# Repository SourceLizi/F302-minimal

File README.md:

# STM32F302C8T6最小系统

这个硬件项目是用于取代原先F103C8T6开发板而制作的，也为其他硬件项目提供参考。相比于同等密度的F103，STM32F302拥有一个高速（5MSPS）ADC，并且额外增加了一个运放和三个比较器，适合模数混合的应用。另外由于其定时器带有输入时钟倍频的功能，其输出分辨率比F103更高。

板载功能除了必须的调试口，复位电路以及晶振电路之外，还引出了USB接口与两枚测试用的LED，另外还增加了一颗IMU（QMI8658C）的位置，用于实践测试IMU解算算法以及评估IMU性能。

最小系统板还配备了一块带有三个半桥驱动的底板（原来的目的是用于驱动电机，后面发现不符合要求），适合用于作为功率级使用。三个半桥均带有电流检测的功能。由核心板的5V经过升压达到11V输入驱动IC，而电流检测放大器的供电则由5V经线性稳压供电。

## 硬件说明

1. 最小系统板内主控的模拟电源与数字电源可分开供电，可以选择使用额外的LDO LP5907为模拟电源供电，或者拖锡连接JP1直接连接模数电源

2. AMS1117输入输出的二极管D3必须焊接，否则会出现在调试时只接入3.3V而1117发热严重的情况

3. IMU的中断管脚INT1与栅极驱动底板的驱动输入引脚有冲突，按照目前的设计二选其一使用

## 软件说明

`f302_minimal_test` 内为早期测试核心板的代码，基本没有实际用途

`imu_f302` 内为IMU测试解算代码，读取QMI8658C解算角度，并将其通过USB虚拟串口发送至匿名地面站上位机。EKF解算算法详见[这篇博客](https://sourcelizi.github.io/202304/imu-practice/)，新增加的ESKF解算算法见[这篇博客](https://sourcelizi.github.io/202311/imu-practice3/)

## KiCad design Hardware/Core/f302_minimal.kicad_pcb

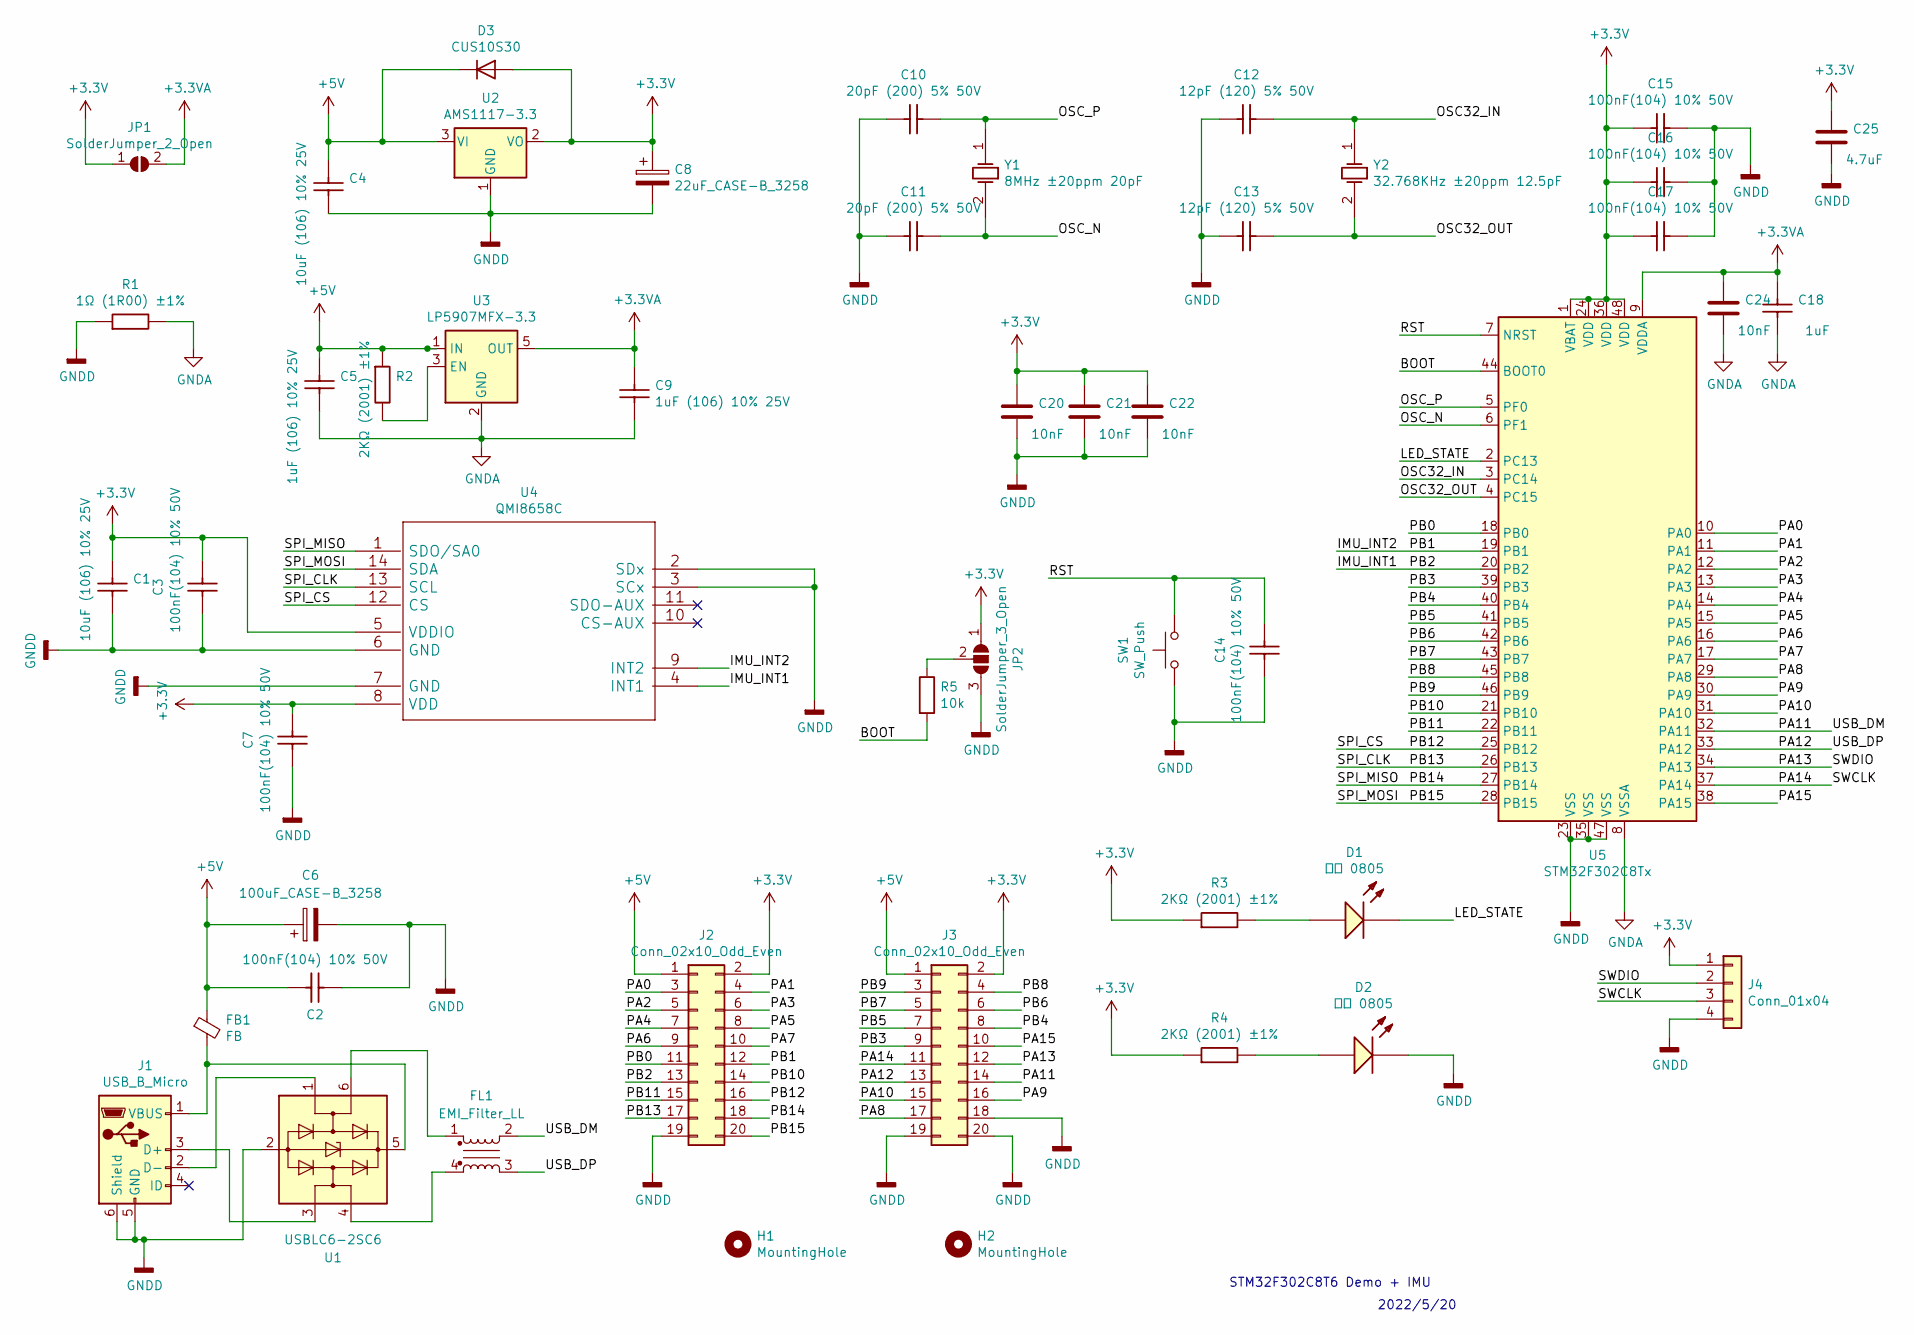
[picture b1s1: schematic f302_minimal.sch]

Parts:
C1, C4, C5, C9: 0805_10uF__106_10%_25V; 0805_C
C2, C3, C7, C14, C15, C16, C17: 0805_100nF_104_10%_50V; 0805_C
C6: 100uF_CASE-B_3258; CP_EIA-3528-21_Kemet-B_Pad1.50x2.35mm_HandSolder
C8: 22uF_CASE-B_3258; CP_EIA-3528-21_Kemet-B_Pad1.50x2.35mm_HandSolder
C10, C11: 0805_20pF__200_5%_50V; 0805_C
C12, C13: 0805_12pF__120_5%_50V; 0603_C
C18: 1uF; 0805_C
C20, C21, C22, C24: 10nF; C_0603_1608Metric_Pad1.08x0.95mm_HandSolder
C25: 4.7uF; C_0805_2012Metric_Pad1.18x1.45mm_HandSolder
D1: 0805_翠绿; 0805_LED_S1
D2: 0805_红灯; 0805_LED_S1
D3: CUS10S30; D_SOD-323_HandSoldering
FB1: FB; R_0805_2012Metric_Pad1.20x1.40mm_HandSolder
FL1: EMI_Filter_LL; DLW21SN900SQ2L
H1, H2: MountingHole; MountingHole_2.2mm_M2_Pad_Via
J1: USB_B_Micro; USB_MicroB
J2, J3: Conn_02x10_Odd_Even; PinHeader_2x10_P2.54mm_Vertical
J4: Conn_01x04; PinHeader_1x04_P2.54mm_Horizontal
JP1: SolderJumper_2_Open; SolderJumper-2_P1.3mm_Open_RoundedPad1.0x1.5mm
JP2: SolderJumper_3_Open; SolderJumper-3_P1.3mm_Open_RoundedPad1.0x1.5mm_NumberLabels
R1: 0603_1Ω__1R00_1%; 0603_R
R2, R3, R4: 0805_2KΩ__2001_1%; 0805_R
R5: 10k; R_0603_1608Metric_Pad0.98x0.95mm_HandSolder
SW1: SW_Push; SW_SPST_CK_RS282G05A3
U1: USBLC6-2SC6; SOT-23-6_Handsoldering
U2: AMS1117-3.3; SOT-223-3_TabPin2
U3: LP5907MFX-3.3; SOT-23-5
U4: QMI8658C; Bosch_LGA-14_3x2.5mm_P0.5mm
U5: STM32F302C8Tx; LQFP-48_7x7mm_P0.5mm
Y1: SMD-5032_2P_8MHz_20ppm_20pF; SMD-5032_2P
Y2: SMD-3215_2P_32.768KHz_20ppm_12.5pF; SMD-3215_2P_FC_-_135

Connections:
+3.3VA: C9.2, C18.1, C24.1, JP1.2 (B), U3.5 (OUT), U5.9 (VDDA)
+3V3: C1.1, C3.2, C7.2, C8.1, C15.1, C16.1, C17.1, C20.1, C21.1, C22.1, C25.1, D3.2 (A), J2.2, J3.2, J4.1, JP1.1 (A), JP2.1 (A), R3.1, R4.1, U2.2 (VO), U4.5 (VDDIO), U4.8 (VDD), U5.1 (VBAT), U5.24 (VDD), U5.36 (VDD), U5.48 (VDD)
+5V: C2.1, C4.1, C5.2, C6.1, D3.1 (K), FB1.1, J2.1, J3.1, R2.1, U2.3 (VI), U3.1 (IN)
/BOOT: R5.2, U5.44 (BOOT0)
/IMU_INT1: J2.13, U4.4 (INT1), U5.20 (PB2)
/IMU_INT2: J2.12, U4.9 (INT2), U5.19 (PB1)
/LED_STATE: D1.K, U5.2 (PC13)
/OSC32_IN: C12.2, U5.3 (PC14), Y2.1 (OSC1)
/OSC32_OUT: C13.2, U5.4 (PC15), Y2.2 (OSC2)
/OSC_N: C11.2, U5.6 (PF1), Y1.2 (OSC2)
/OSC_P: C10.2, U5.5 (PF0), Y1.1 (OSC1)
/PA0: J2.3, U5.10 (PA0)
/PA1: J2.4, U5.11 (PA1)
/PA2: J2.5, U5.12 (PA2)
/PA3: J2.6, U5.13 (PA3)
/PA4: J2.7, U5.14 (PA4)
/PA5: J2.8, U5.15 (PA5)
/PA6: J2.9, U5.16 (PA6)
/PA7: J2.10, U5.17 (PA7)
/PA8: J3.17, U5.29 (PA8)
/PA9: J3.16, U5.30 (PA9)
/PA10: J3.15, U5.31 (PA10)
/PA11: FL1.2, J3.14, U5.32 (PA11)
/PA12: FL1.3, J3.13, U5.33 (PA12)
/PA13: J3.12, J4.2, U5.34 (PA13)
/PA14: J3.11, J4.3, U5.37 (PA14)
/PA15: J3.10, U5.38 (PA15)
/PB0: J2.11, U5.18 (PB0)
/PB3: J3.9, U5.39 (PB3)
/PB4: J3.8, U5.40 (PB4)
/PB5: J3.7, U5.41 (PB5)
/PB6: J3.6, U5.42 (PB6)
/PB7: J3.5, U5.43 (PB7)
/PB8: J3.4, U5.45 (PB8)
/PB9: J3.3, U5.46 (PB9)
/PB10: J2.14, U5.21 (PB10)
/PB11: J2.15, U5.22 (PB11)
/PB12: J2.16, U4.12 (CS), U5.25 (PB12)
/PB13: J2.17, U4.13 (SCL), U5.26 (PB13)
/PB14: J2.18, U4.1 (SDO/SA0), U5.27 (PB14)
/PB15: J2.20, U4.14 (SDA), U5.28 (PB15)
/RST: C14.2, SW1.2, U5.7 (NRST)
GNDA: C5.1, C9.1, C18.2, C24.2, R1.2, U3.2 (GND), U5.8 (VSSA)
GNDD: C1.2, C2.2, C3.1, C4.2, C6.2, C7.1, C8.2, C10.1, C11.1, C12.1, C13.1, C14.1, C15.2, C16.2, C17.2, C20.2, C21.2, C22.2, C25.2, D2.K, J1.5 (GND), J1.6 (Shield), J2.19, J3.18, J3.19, J3.20, J4.4, JP2.3 (B), R1.1, SW1.1, U1.2 (GND), U2.1 (GND), U4.2 (SDx), U4.3 (SCx), U4.6 (GND), U4.7 (GND), U5.23 (VSS), U5.35 (VSS), U5.47 (VSS); also elsewhere on the board
unnamed: D1.A, R3.2
unnamed: D2.A, R4.2
unnamed 46: FB1.2, J1.1 (VBUS), U1.5 (VBUS); also elsewhere on the board
unnamed: FL1.1, U1.6 (I/O1)
unnamed: FL1.4, U1.4 (I/O2)
unnamed 49: J1.2 (D-), U1.1 (I/O1); also elsewhere on the board
unnamed 50: J1.3 (D+), U1.3 (I/O2); also elsewhere on the board
unnamed 51: J1.4 (ID); also elsewhere on the board
unnamed: JP2.2 (C), R5.1
unnamed: R2.2, U3.3 (EN)

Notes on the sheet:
STM32F302C8T6 Demo + IMU
2022/5/20

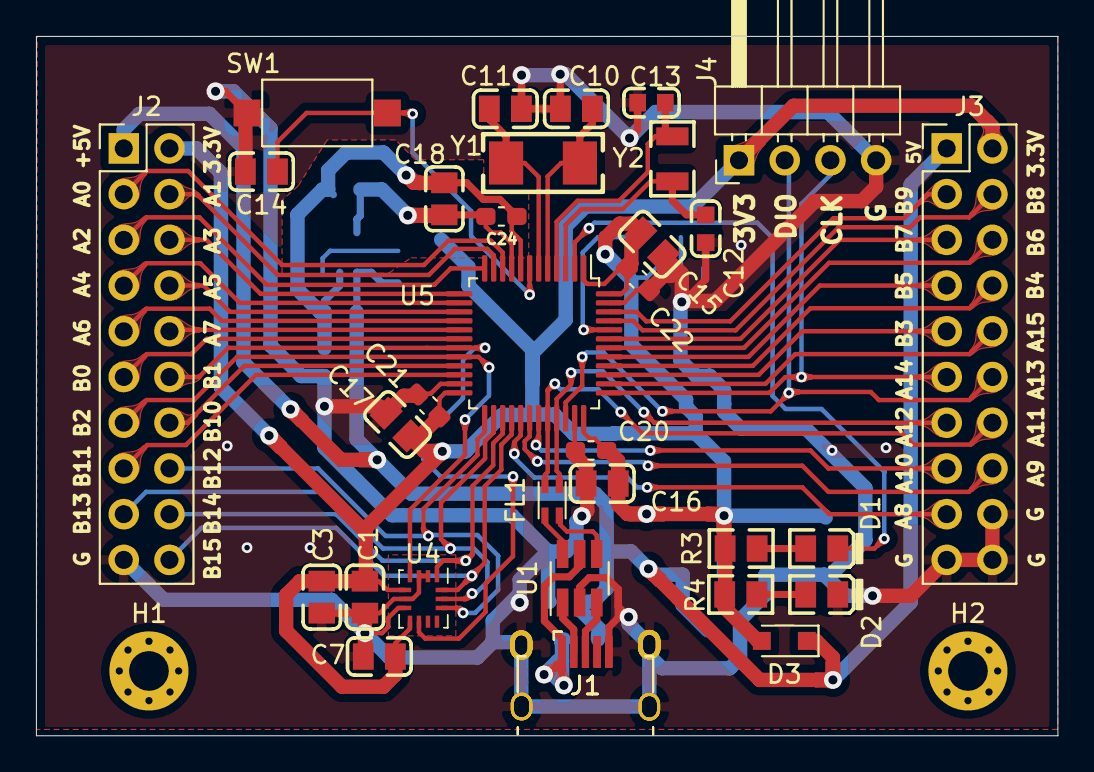
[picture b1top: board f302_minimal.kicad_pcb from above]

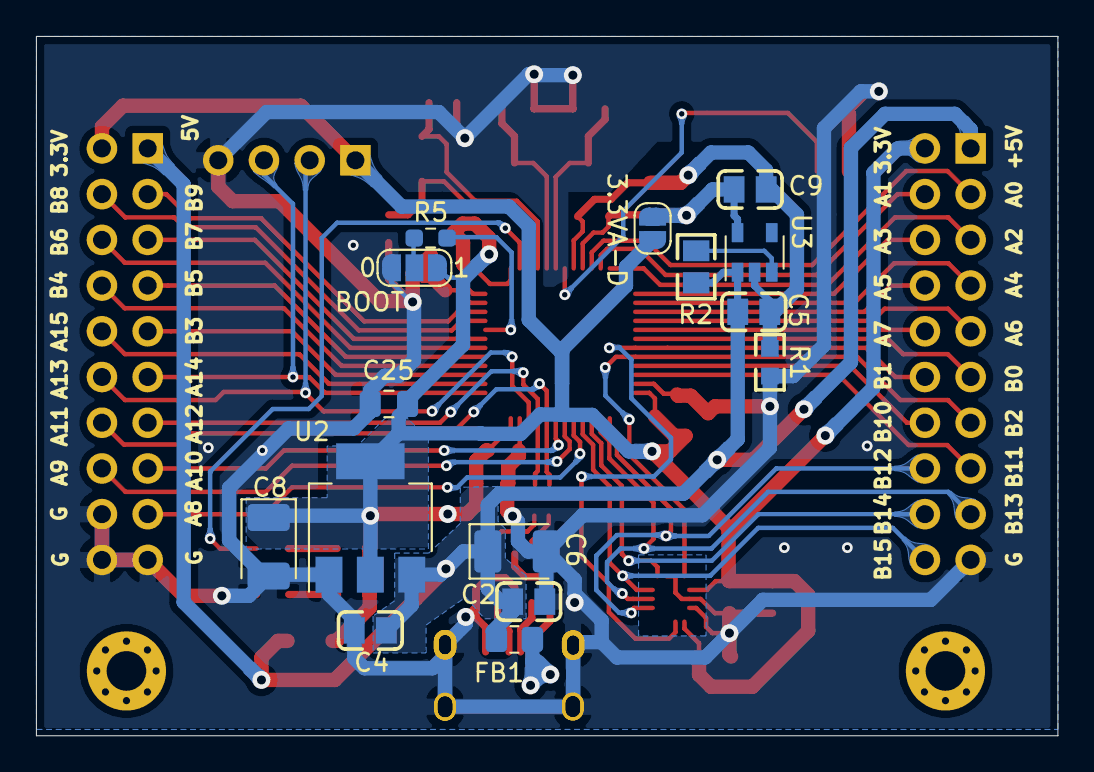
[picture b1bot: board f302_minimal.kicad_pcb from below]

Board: 2 copper layers, 56.8 x 38.8 mm, 50 parts (15 on the bottom side), 54 nets.

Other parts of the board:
J1#2: USB_B_Micro; USB_MicroB

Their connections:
GNDD: J1#2.5, J1#2.6; also elsewhere on the board
unnamed 46: J1#2.1; also elsewhere on the board
unnamed 49: J1#2.2; also elsewhere on the board
unnamed 50: J1#2.3; also elsewhere on the board
unnamed 51: J1#2.4; also elsewhere on the board

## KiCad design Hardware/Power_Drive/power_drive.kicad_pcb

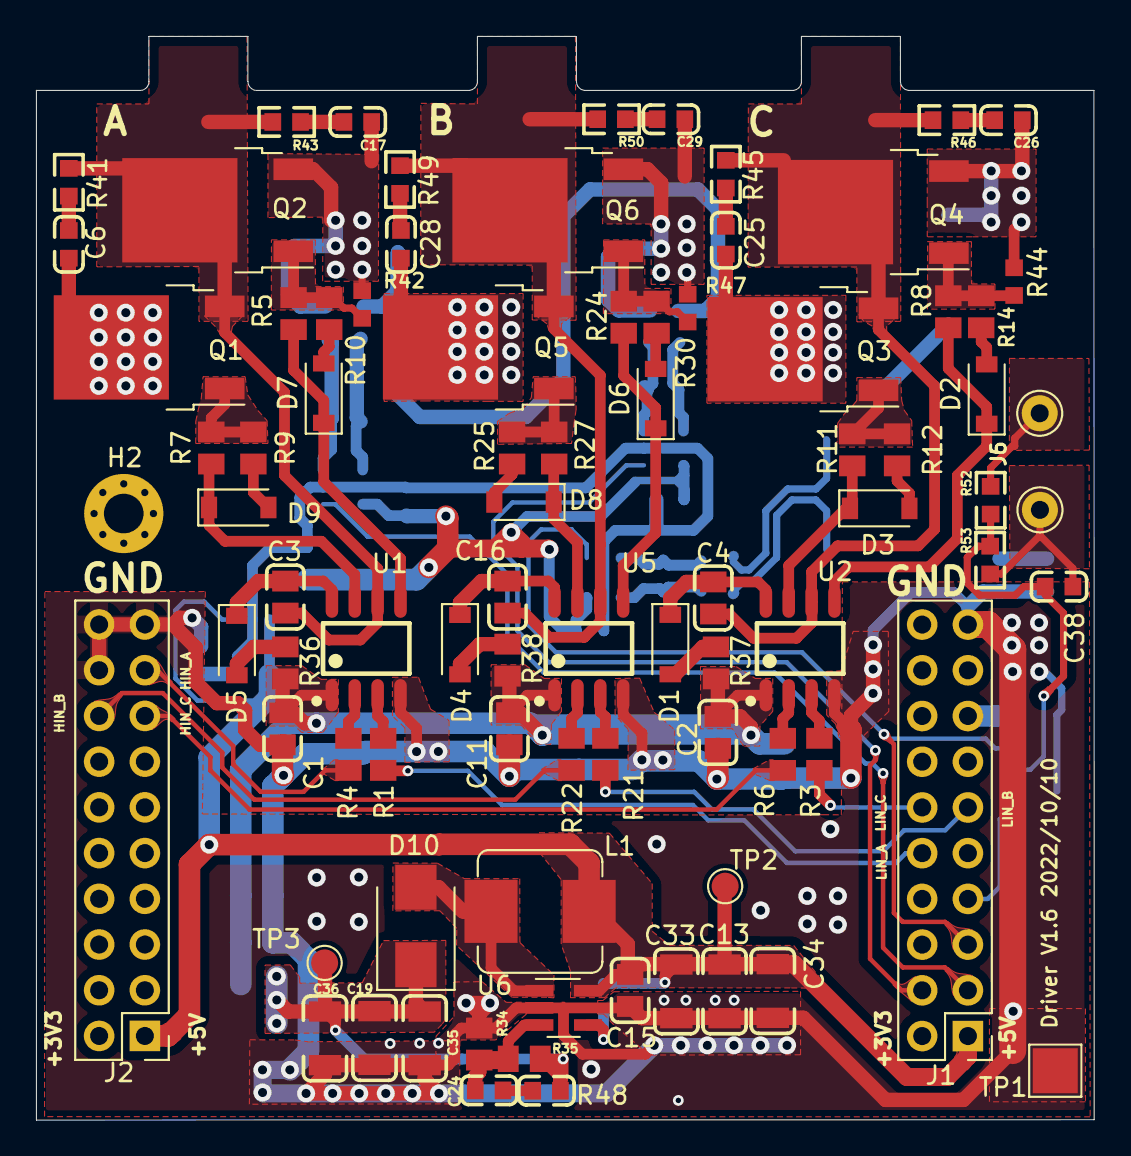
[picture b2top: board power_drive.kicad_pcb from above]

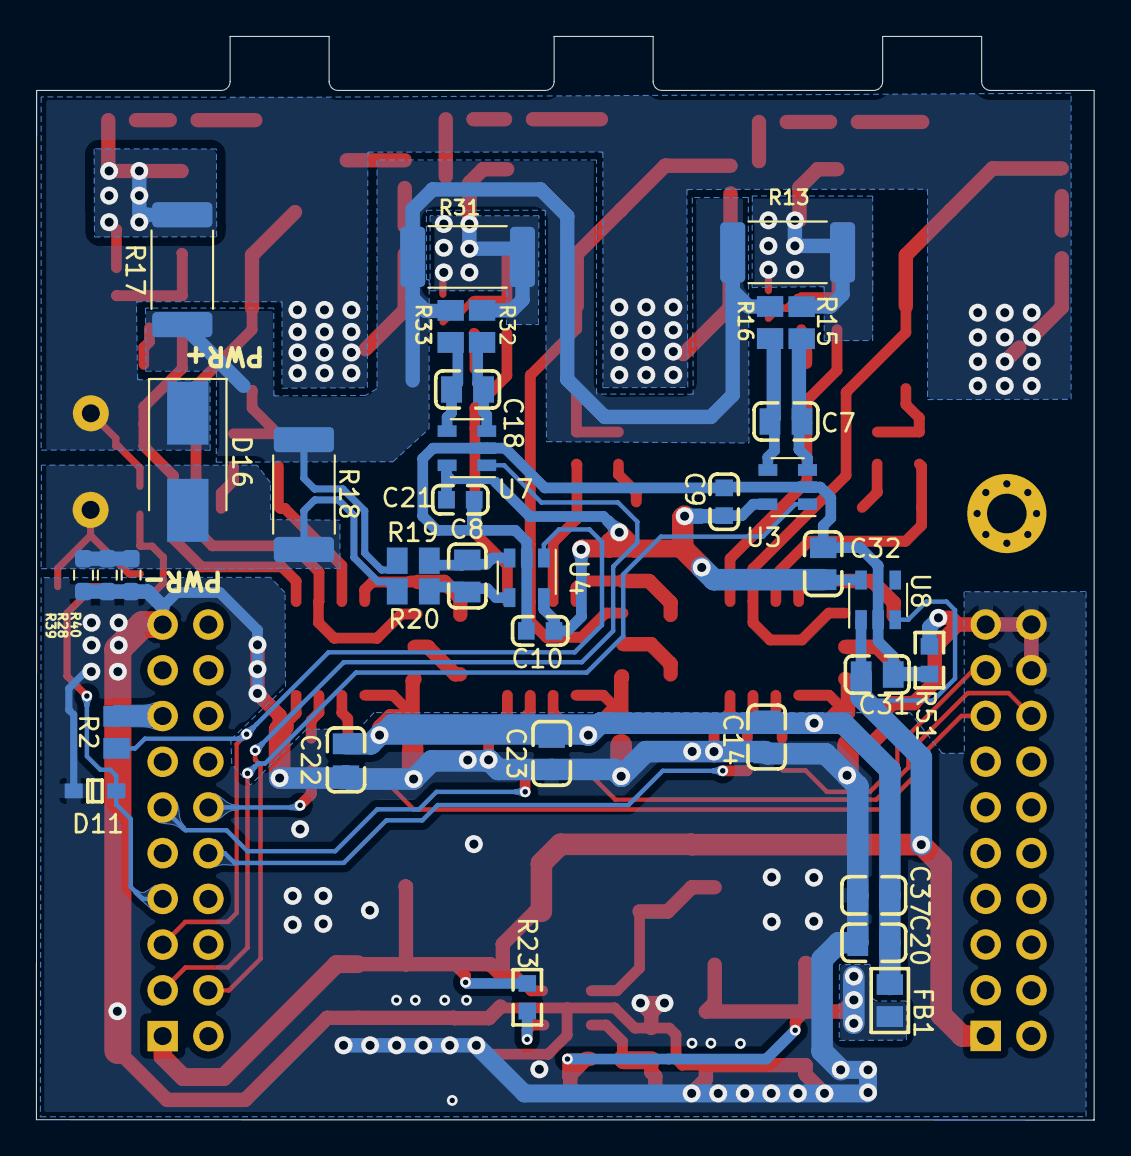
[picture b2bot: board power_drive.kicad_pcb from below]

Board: 2 copper layers, 58.8 x 60.2 mm, 121 parts (36 on the bottom side), 72 nets.

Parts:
C1, C2, C11, C15, C20: 100nF; 0805_C
C3, C4, C16, C31, C32: 1uF; 0805_C
C6, C17, C25, C26, C28, C29: 1uF; 0603_C
C7, C8, C18: 4.7uF; 0805_C
C9, C10, C21, C38: 100nF; 0603_C
C13, C19, C33, C34, C35, C36: 22uF; 1206_C
C14, C22, C23: 22uF; 0805_C
C24: 10pF; 0603_C
C37: 10nF; 0805_C
D1, D4, D5: BAT46; D_SOD-123
D2, D3, D6, D7, D8, D9: 1N4148; D_SOD-123
D10: 1N5821; D_SMB
D11: D_TVS; SOD-323
D16: D_ALT; D_SMB_Handsoldering
FB1: Ferrite_Bead; 0805_L
H2: MountingHole; MountingHole_2.2mm_M2_Pad_Via
J1, J2: Conn_02x10_Odd_Even; PinHeader_2x10_P2.54mm_Vertical
J5, J6: Conn_01x01; Pin_D1.0mm_L10.0mm
L1: 10uH; L_Bourns_SRP7028A_7.3x6.6mm
Q1, Q2, Q3, Q4, Q5, Q6: Q_NMOS_GDS; TO-252-2
R1, R2, R3, R4, R6, R21, R22, R36, R37, R38: 5R; 0805
R5, R7, R8, R11, R24, R25: 20R; 0805
R9, R10, R12, R14, R27, R30: 51R; 0805
R13, R17, R18, R31: 0.01; R_2512_6332Metric_Pad1.40x3.35mm_HandSolder
R15, R16, R19, R20, R32, R33: 1R; 0805
R23: 5k; 0603_R
R28, R39, R40: 0603_0Ω__0R0_1%; R_0603_1608Metric_Pad0.98x0.95mm_HandSolder
R34: 6.8k; 0805
R35: 51k; 0805
R41, R43, R45, R46, R49, R50: 10R; 0603_R
R42, R44, R47: 51k; 0603
R48: 0R; 0603_C
R51: 0603_0Ω__0R0_1%; 0603_R
R52: 470k; 0603_R
R53: 33k; 0603_R
TP1: TestPoint; TestPoint_Pad_2.5x2.5mm
TP2, TP3: TestPoint; TestPoint_Pad_D1.5mm
U1, U2, U5: IR2101; SOP-8_150MIL
U3, U4, U7: INA180; SOT-23-5
U6: MT3540; SOT-23-5_HandSoldering
U8: LP5907MFX-3.3; SOT-23-5

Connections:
+3V3: C9.2, C10.2, C21.2, C32.2, U3.5, U4.5, U7.5, U8.5
+5V: C13.2, C15.2, C31.2, C33.2, C34.2, J1.1, J2.1, L1.1, R23.1, TP2.1, U6.5, U8.1, U8.3
/HIN_A: J2.17, R4.1
/HIN_B: J2.16, R22.1
/HIN_C: J2.15, R6.1
/I_SENSE_A: J1.3, U3.1
/I_SENSE_ALL: J1.5, R2.1, U4.1
/I_SENSE_B: J1.4, U7.1
/I_SENSE_GND: R13.1, R16.1, R17.1, R18.2, R19.1, R31.1, R33.1
/LIN_A: J1.10, R1.1
/LIN_B: J1.11, R21.1
/LIN_C: J1.12, R3.1
/PWR_VSENSE: C38.2, D11.1, J1.7, R52.1, R53.1
GNDA: C9.1, C10.1, C21.1, C31.1, C32.1, R51.2, U3.2, U4.2, U7.2, U8.2
GNDD: C1.1, C2.1, C11.1, C13.1, C14.1, C15.1, C19.1, C20.1, C22.1, C23.1, C33.1, C34.1, C35.1, C36.1, C37.1, D11.2, J1.19, J2.18, J2.19, J2.20, R28.2, R34.2, R39.2, R40.2, R51.1, TP1.1, U1.4, U2.4, U5.4, U6.2
GNDPWR: C38.1, D16.2, J6.1, R18.1, R20.1, R28.1, R39.1, R40.1, R53.2
unnamed: C3.1, Q1.3, Q2.2, R41.2, R43.2, U1.6
unnamed: C3.2, D5.1, U1.8
unnamed: C4.1, Q3.3, Q4.2, R45.2, R46.2, U2.6
unnamed: C4.2, D1.1, U2.8
unnamed: C6.1, R41.1
unnamed: C7.1, R16.2, U3.4
unnamed: C7.2, R15.2, U3.3
unnamed: C8.1, R20.2, U4.4
unnamed: C8.2, R19.2, U4.3
unnamed: C16.1, Q5.3, Q6.2, R49.2, R50.2, U5.6
unnamed: C16.2, D4.1, U5.8
unnamed: C17.1, Q2.3, R13.2, R15.1, R42.2
unnamed: C17.2, R43.1
unnamed: C18.1, R33.2, U7.4
unnamed: C18.2, R32.2, U7.3
unnamed: C19.2, C35.2, C36.2, D10.1, FB1.2, R35.1, R48.2, TP3.1
unnamed: C24.1, R48.1
unnamed: C24.2, R34.1, R35.2, U6.3
unnamed: C25.1, R45.1
unnamed: C26.1, Q4.3, R17.2, R44.2
unnamed: C26.2, R46.1
unnamed: C28.1, R49.1
unnamed: C29.1, Q6.3, R31.2, R32.1, R47.2
unnamed: C29.2, R50.1
unnamed: D1.2, R37.1
unnamed: D2.1, R8.2, U2.5
unnamed: D2.2, R14.1
unnamed: D3.1, R11.2, U2.7
unnamed: D3.2, R12.2
unnamed: D4.2, R38.1
unnamed: D5.2, R36.1
unnamed: D6.1, R24.2, U5.5
unnamed: D6.2, R30.1
unnamed: D7.1, R5.2, U1.5
unnamed: D7.2, R10.1
unnamed: D8.1, R25.2, U5.7
unnamed: D8.2, R27.2
unnamed: D9.1, R7.2, U1.7
unnamed: D9.2, R9.2
unnamed: D10.2, L1.2, U6.1
unnamed: J1.15, R2.2
unnamed: Q1.1, R7.1, R9.1
unnamed: Q2.1, R5.1, R10.2, R42.1
unnamed: Q3.1, R11.1, R12.1
unnamed: Q4.1, R8.1, R14.2, R44.1
unnamed: Q5.1, R25.1, R27.1
unnamed: Q6.1, R24.1, R30.2, R47.1
unnamed: R1.2, U1.3
unnamed: R3.2, U2.3
unnamed: R4.2, U1.2
unnamed: R6.2, U2.2
unnamed: R21.2, U5.3
unnamed: R22.2, U5.2
unnamed: R23.2, U6.4
VCC: C1.2, C2.2, C11.2, C14.2, C20.2, C22.2, C23.2, C37.2, FB1.1, R36.2, R37.2, R38.2, U1.1, U2.1, U5.1
Vdrive: C6.2, C25.2, C28.2, D16.1, J5.1, Q1.2, Q3.2, Q5.2, R52.2

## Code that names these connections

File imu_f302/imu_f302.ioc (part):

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Mcu.Name=STM32F302C(6-8)Tx
Mcu.Package=LQFP48
Mcu.UserName=STM32F302C8Tx
PA11.Mode=Device
PA11.Signal=USB_DM
PA12.Mode=Device
PA12.Signal=USB_DP
PA13.Mode=Serial_Wire
PA13.Signal=SYS_JTMS-SWDIO
PA14.Mode=Serial_Wire
PA14.Signal=SYS_JTCK-SWCLK
PB12.Mode=NSS_Signal_Hard_Output
PB12.Signal=SPI2_NSS
PB13.Mode=Full_Duplex_Master
PB13.Signal=SPI2_SCK
PB14.Mode=Full_Duplex_Master
PB14.Signal=SPI2_MISO
PB15.Mode=Full_Duplex_Master
PB15.Signal=SPI2_MOSI
PC13.GPIOParameters=PinState
PC13.PinState=GPIO_PIN_SET
PC13.Signal=GPIO_Output
PF0-OSC_IN.Mode=HSE-External-Oscillator
PF0-OSC_IN.Signal=RCC_OSC_IN
PF1-OSC_OUT.Mode=HSE-External-Oscillator
PF1-OSC_OUT.Signal=RCC_OSC_OUT
RCC.HSEPLLFreq_Value=8000000
RCC.HSE_VALUE=8000000
RCC.SYSCLKFreq_VALUE=72000000
RCC.SYSCLKSourceVirtual=RCC_SYSCLKSOURCE_PLLCLK
board=custom

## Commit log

2022-07-05 init files
2023-05-05 hardware updated, add imu fusion code
2023-05-05 add readme
2024-01-26 update hardware, add eskf code, bug fix
